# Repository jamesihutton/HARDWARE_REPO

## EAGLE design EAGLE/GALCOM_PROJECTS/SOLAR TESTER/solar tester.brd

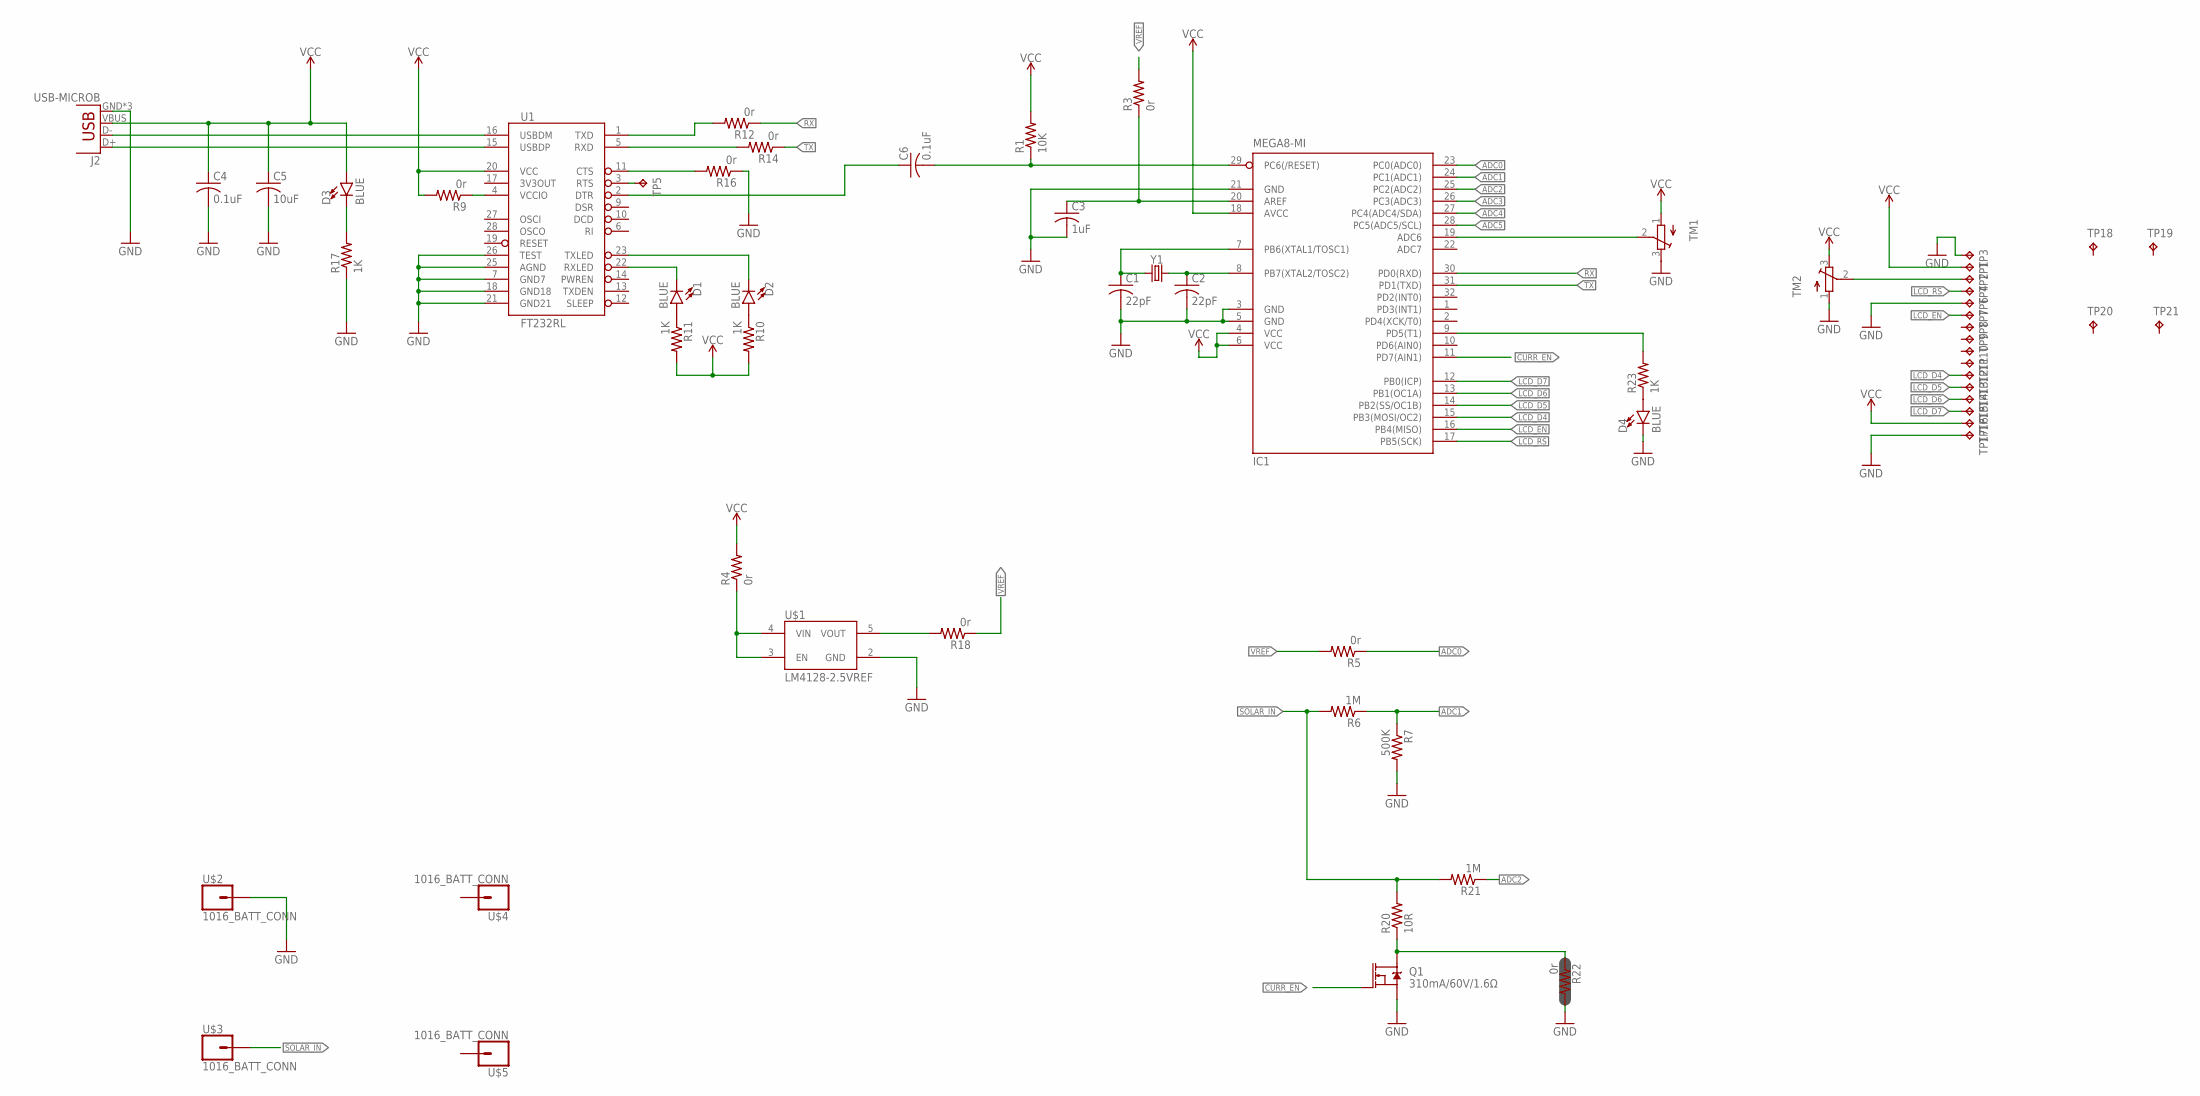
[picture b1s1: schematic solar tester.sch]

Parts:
C1, C2: 22pF; C0402
C3: 1uF; C0402
C4, C6: 0.1uF; C0402
C5: 10uF; C0402
D1, D2, D3, D4: BLUE; LED-0603
IC1: MEGA8-MI; MLF32
J2: USB-MICROB
Q1: 310mA/60V/1.6Ω; SOT323
R1: 10K; R0402
R3, R4, R5, R9, R12, R14, R16, R18, R22: 0r; R0402
R6, R21: 1M; R0402
R7: 500K; R0402
R10, R11, R17, R23: 1K; R0402
R20: 10R; M1206
TM1, TM2: TRIMPOTTC33X; TC33X
TP1, TP2, TP3, TP4, TP6, TP7, TP8, TP9, TP10, TP11, TP12, TP13, TP14, TP15, TP16, TP17: TPTP19R; TP19R
TP5: TPB1,27; B1,27
TP18, TP19, TP20, TP21: TPB2,54; B2,54
U1: FT232RL; SSOP28DB
U$1: LM4128-2.5VREF; SOT23-5
U$2, U$3, U$4, U$5: 1016_BATT_CONN; 1016_BATTERY_CONNECTOR
Y1: CRYSTALSMD-3.2X2.5; CRYSTAL-SMD-3.2X2.5MM

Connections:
ADC0: IC1.23 (PC0(ADC0)), R5.1
ADC1: IC1.24 (PC1(ADC1)), R6.1, R7.1
ADC2: IC1.25 (PC2(ADC2)), R21.1
ADC3: IC1.26 (PC3(ADC3))
ADC4: IC1.27 (PC4(ADC4/SDA))
ADC5: IC1.28 (PC5(ADC5/SCL))
CURR_EN: IC1.11 (PD7(AIN1)), Q1.1 (G)
GND: C1.2, C2.2, C3.2, C4.2, C5.2, D4.C, IC1.3 (GND), IC1.5 (GND), IC1.21 (GND), J2.GND, J2.MT1 (GND), J2.MT2 (GND), Q1.2 (S), R7.2, R16.1, R17.1, R22.2, TM1.3 (E), TM2.1 (A), TP3.TP, TP6.TP, TP17.TP, U1.7 (GND7), U1.18 (GND18), U1.21 (GND21), U1.25 (AGND), U1.26 (TEST), U$1.2 (GND), U$2.P$1
LCD_D4: IC1.15 (PB3(MOSI/OC2)), TP12.TP
LCD_D5: IC1.14 (PB2(SS/OC1B)), TP13.TP
LCD_D6: IC1.13 (PB1(OC1A)), TP14.TP
LCD_D7: IC1.12 (PB0(ICP)), TP15.TP
LCD_EN: IC1.16 (PB4(MISO)), TP7.TP
LCD_RS: IC1.17 (PB5(SCK)), TP4.TP
unnamed: C1.1, IC1.7 (PB6(XTAL1/TOSC1)), Y1.1
unnamed: C2.1, IC1.8 (PB7(XTAL2/TOSC2)), Y1.3 (2)
unnamed: R4.1, U$1.3 (EN), U$1.4 (VIN)
unnamed: D1.A, R11.1
unnamed: TM2.2 (S), TP2.TP
unnamed: D2.A, R10.1
unnamed: J2.D-, U1.16 (USBDM)
unnamed: J2.D+, U1.15 (USBDP)
unnamed: D3.C, R17.2
unnamed: D1.C, U1.22 (RXLED)
unnamed: R9.1, U1.4 (VCCIO)
unnamed: D2.C, U1.23 (TXLED)
unnamed: R16.2, U1.11 (CTS)
unnamed: R12.2, U1.1 (TXD)
unnamed: R14.2, U1.5 (RXD)
unnamed: C6.1, U1.2 (DTR)
unnamed: R18.2, U$1.5 (VOUT)
unnamed: Q1.3 (D), R20.1, R22.1
unnamed: IC1.19 (ADC6), TM1.2 (S)
unnamed: D4.A, R23.1
unnamed: IC1.9 (PD5(T1)), R23.2
unnamed: C3.1, IC1.20 (AREF), R3.1
unnamed: TP5.TP, U1.3 (RTS)
RST: C6.2, IC1.29 (PC6(/RESET)), R1.1
RX: IC1.30 (PD0(RXD)), R12.1
SOLAR_IN: R6.2, R20.2, R21.2, U$3.P$1
TX: IC1.31 (PD1(TXD)), R14.1
VCC: C4.1, C5.1, D3.A, IC1.4 (VCC), IC1.6 (VCC), IC1.18 (AVCC), J2.VBUS, R1.2, R4.2, R9.2, R10.2, R11.2, TM1.1 (A), TM2.3 (E), TP1.TP, TP16.TP, U1.20 (VCC)
VREF: R3.2, R5.2, R18.1

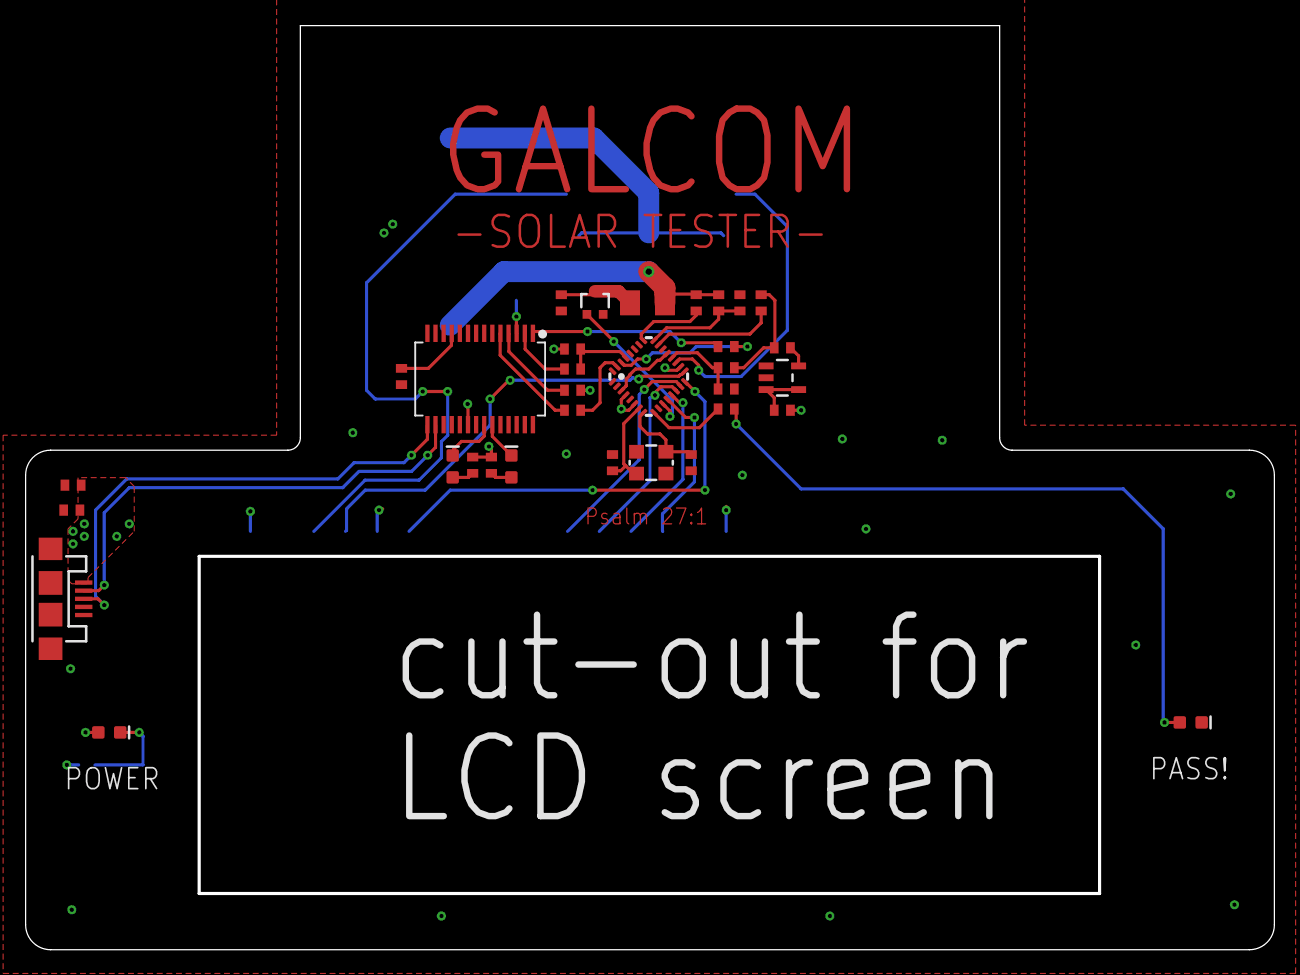
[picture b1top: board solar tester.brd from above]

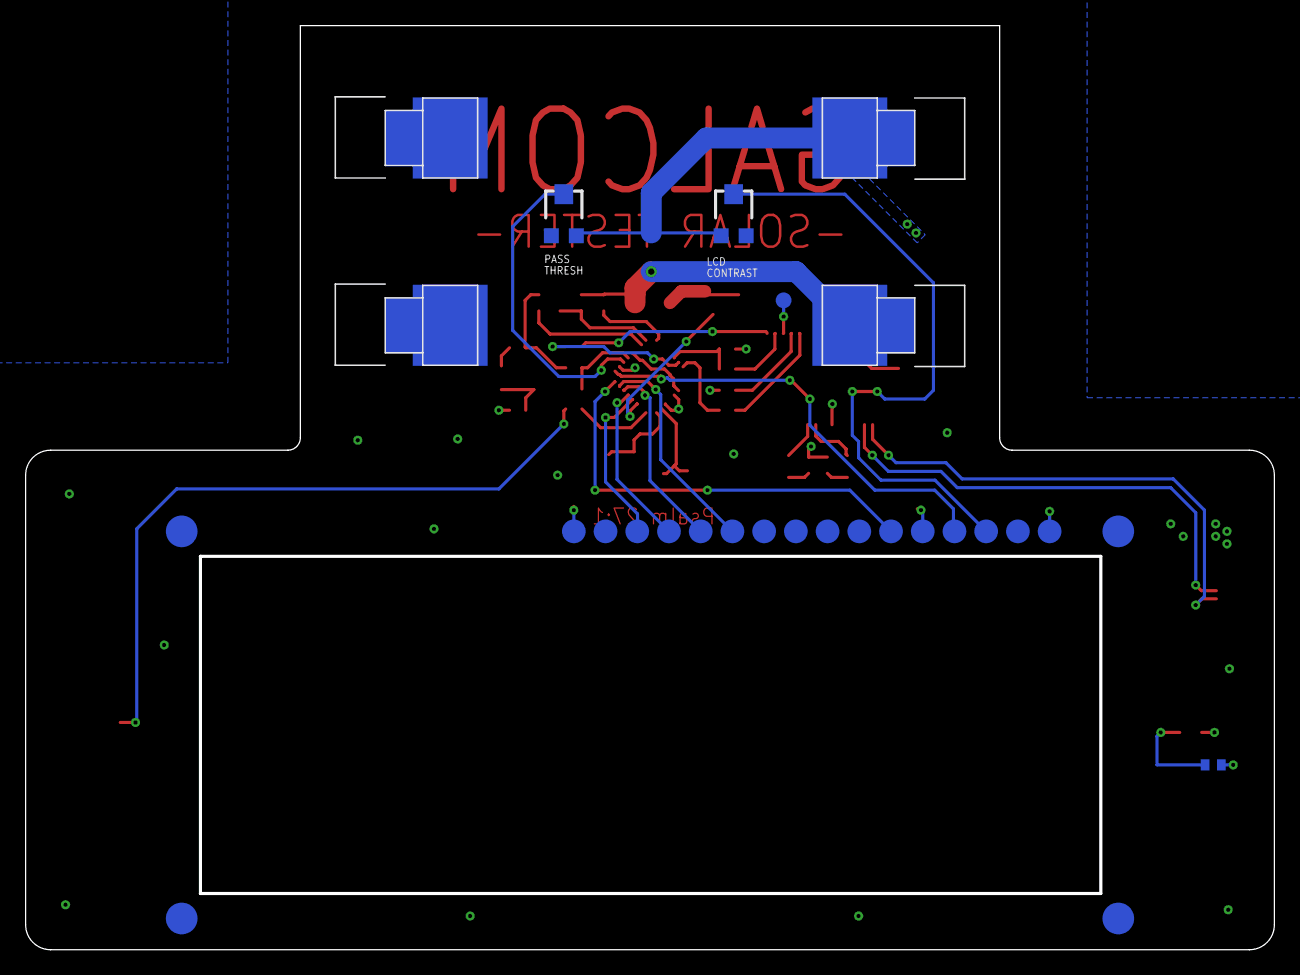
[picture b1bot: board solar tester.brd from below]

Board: 2 copper layers, 99.8 x 73.8 mm, 61 parts (28 on the bottom side), 40 nets.

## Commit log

2019-09-16 setup files
2019-09-16 init Library and proto1.0

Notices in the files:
parts and their libraries:
SparkFun-Clocks: Licensing: Creative Commons ShareAlike 4.0 International - https://creativecommons.org/licenses/by-sa/4.0
